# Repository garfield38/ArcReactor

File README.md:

# ArcReactor
Arc Reactor replica made with Attiny85 and WS2812B LEDs

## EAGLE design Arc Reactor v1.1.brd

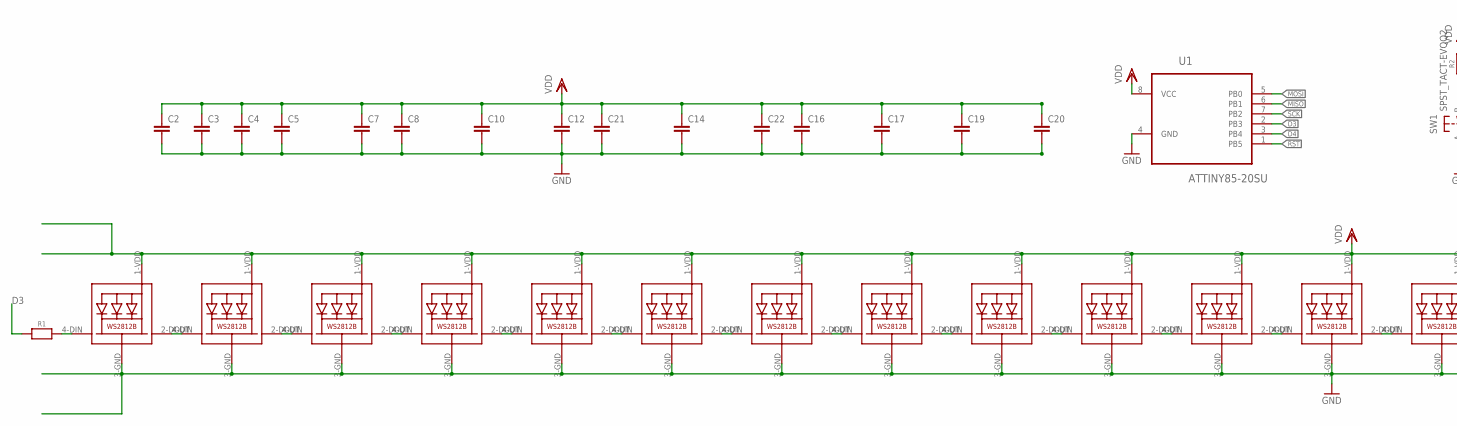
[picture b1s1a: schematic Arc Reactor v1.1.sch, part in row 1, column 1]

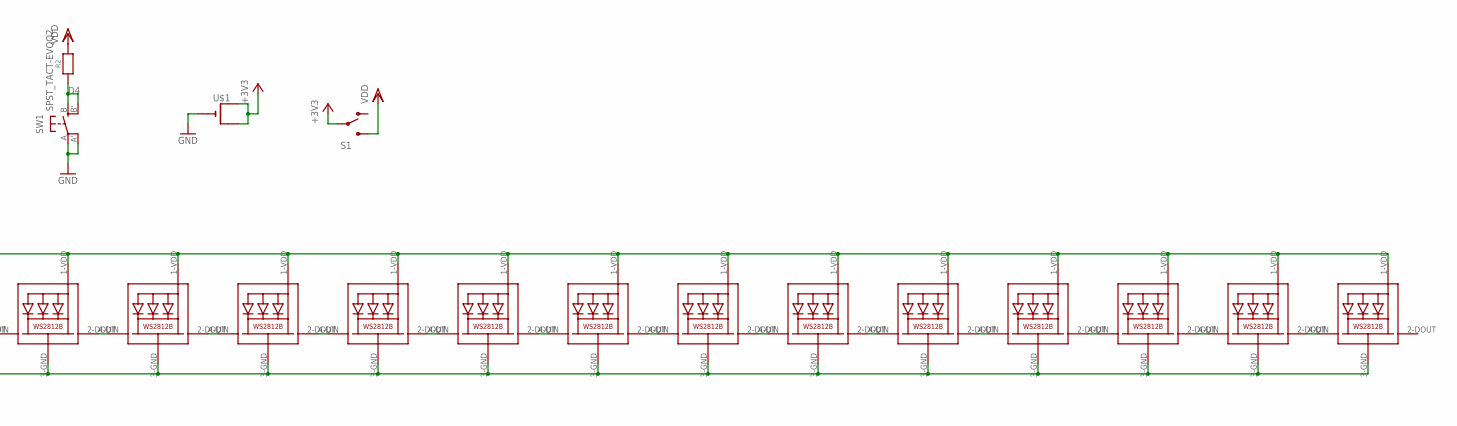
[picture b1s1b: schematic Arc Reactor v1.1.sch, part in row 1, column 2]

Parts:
C2, C3, C4, C5, C7, C8, C10, C12, C14, C16, C17, C19, C20, C21, C22: C-EUC0603; C0603; MOUSER# 77-VJ0603Y104JXQPBC
LED1, LED3, LED4, LED5, LED6, LED7, LED8, LED9, LED10, LED11, LED12, LED13, LED14, LED15, LED16, LED17, LED18, LED19, LED20, LED21, LED22, LED23, LED24, LED25, LED26: WS2812B5050; WS2812B
R1, R2: RESISTOR_0603_NOOUT; 0603-NO
S1: SWITCH-SPDTSMD2; SWITCH-SPDT-SMD; MOUSER# 611-JS102011SAQN
SW1: SPST_TACT-EVQQ2; EVQ-Q2
U1: ATTINY85-20SU; SOIC127P798X216-8N; MOUSER# 556-ATTINY85-20SU
U$1: CR2032SMT; CR2032-SMD

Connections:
+3V3: S1.2, U$1.+$1 (+), U$1.+$2 (+1)
D3: R1.1, U1.2 (PB3)
D4: R2.1, SW1.B (S), SW1.B' (S1), U1.3 (PB4)
GND: C2.2, C3.2, C4.2, C5.2, C7.2, C8.2, C10.2, C12.2, C14.2, C16.2, C17.2, C19.2, C20.2, C21.2, C22.2, LED1.3-GND (GND), LED3.3-GND (GND), LED4.3-GND (GND), LED5.3-GND (GND), LED6.3-GND (GND), LED7.3-GND (GND), LED8.3-GND (GND), LED9.3-GND (GND), LED10.3-GND (GND), LED11.3-GND (GND), LED12.3-GND (GND), LED13.3-GND (GND), LED14.3-GND (GND), LED15.3-GND (GND), LED16.3-GND (GND), LED17.3-GND (GND), LED18.3-GND (GND), LED19.3-GND (GND), LED20.3-GND (GND), LED21.3-GND (GND), LED22.3-GND (GND), LED23.3-GND (GND), LED24.3-GND (GND), LED25.3-GND (GND), LED26.3-GND (GND), SW1.A, SW1.A' (P1), U1.4 (GND), U$1.-
MISO: U1.6 (PB1)
MOSI: U1.5 (PB0)
unnamed: LED1.2-DOUT (DO), LED3.4-DIN (DI)
unnamed: LED3.2-DOUT (DO), LED4.4-DIN (DI)
unnamed: LED4.2-DOUT (DO), LED5.4-DIN (DI)
unnamed: LED5.2-DOUT (DO), LED6.4-DIN (DI)
unnamed: LED6.2-DOUT (DO), LED7.4-DIN (DI)
unnamed: LED7.2-DOUT (DO), LED8.4-DIN (DI)
unnamed: LED8.2-DOUT (DO), LED9.4-DIN (DI)
unnamed: LED9.2-DOUT (DO), LED10.4-DIN (DI)
unnamed: LED10.2-DOUT (DO), LED11.4-DIN (DI)
unnamed: LED11.2-DOUT (DO), LED12.4-DIN (DI)
unnamed: LED12.2-DOUT (DO), LED13.4-DIN (DI)
unnamed: LED13.2-DOUT (DO), LED14.4-DIN (DI)
unnamed: LED14.2-DOUT (DO), LED15.4-DIN (DI)
unnamed: LED15.2-DOUT (DO), LED16.4-DIN (DI)
unnamed: LED16.2-DOUT (DO), LED17.4-DIN (DI)
unnamed: LED17.2-DOUT (DO), LED18.4-DIN (DI)
unnamed: LED18.2-DOUT (DO), LED19.4-DIN (DI)
unnamed: LED19.2-DOUT (DO), LED20.4-DIN (DI)
unnamed: LED20.2-DOUT (DO), LED21.4-DIN (DI)
unnamed: LED21.2-DOUT (DO), LED22.4-DIN (DI)
unnamed: LED22.2-DOUT (DO), LED23.4-DIN (DI)
unnamed: LED23.2-DOUT (DO), LED24.4-DIN (DI)
unnamed: LED24.2-DOUT (DO), LED25.4-DIN (DI)
unnamed: LED25.2-DOUT (DO), LED26.4-DIN (DI)
unnamed: LED1.4-DIN (DI), R1.2
RST: U1.1 (PB5)
SCK: U1.7 (PB2)
VDD: C2.1, C3.1, C4.1, C5.1, C7.1, C8.1, C10.1, C12.1, C14.1, C16.1, C17.1, C19.1, C20.1, C21.1, C22.1, LED1.1-VDD (VDD), LED3.1-VDD (VDD), LED4.1-VDD (VDD), LED5.1-VDD (VDD), LED6.1-VDD (VDD), LED7.1-VDD (VDD), LED8.1-VDD (VDD), LED9.1-VDD (VDD), LED10.1-VDD (VDD), LED11.1-VDD (VDD), LED12.1-VDD (VDD), LED13.1-VDD (VDD), LED14.1-VDD (VDD), LED15.1-VDD (VDD), LED16.1-VDD (VDD), LED17.1-VDD (VDD), LED18.1-VDD (VDD), LED19.1-VDD (VDD), LED20.1-VDD (VDD), LED21.1-VDD (VDD), LED22.1-VDD (VDD), LED23.1-VDD (VDD), LED24.1-VDD (VDD), LED25.1-VDD (VDD), LED26.1-VDD (VDD), R2.2, S1.3 (S), U1.8 (VCC)

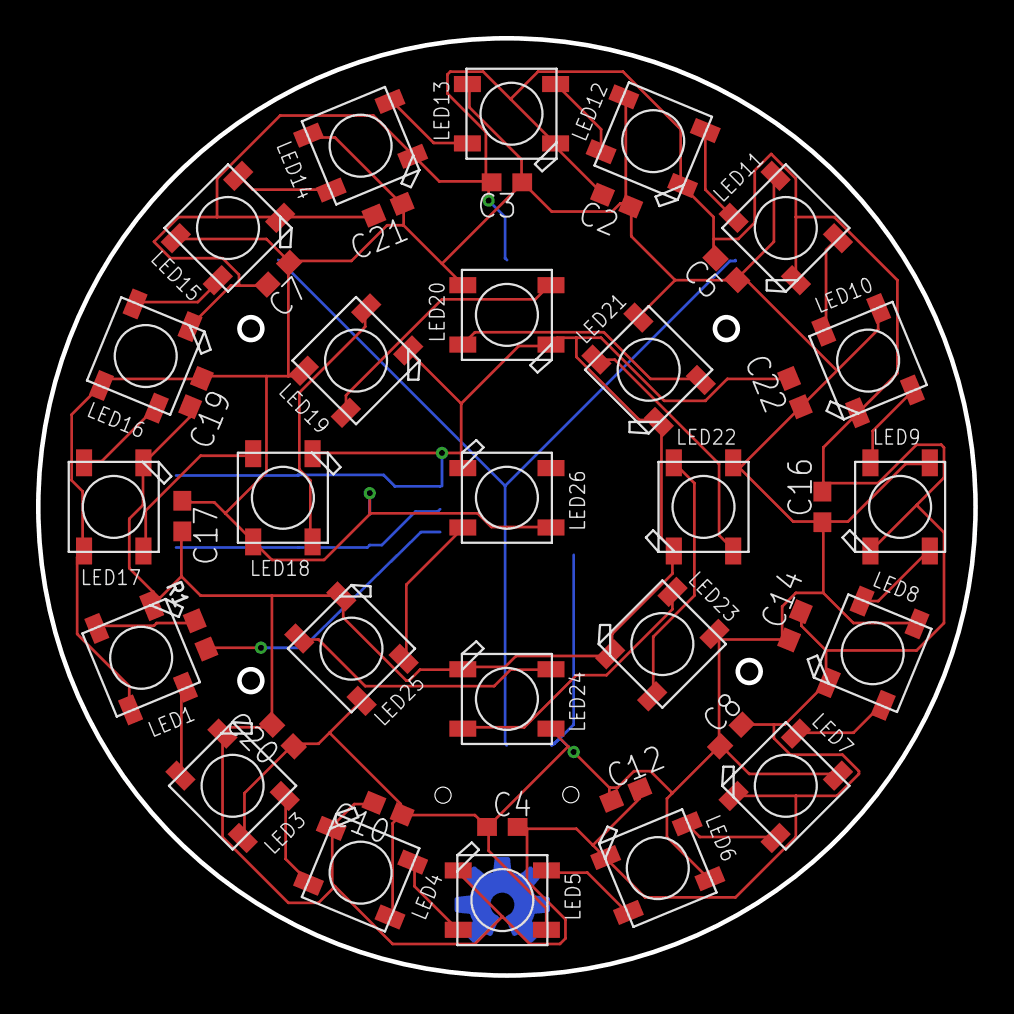
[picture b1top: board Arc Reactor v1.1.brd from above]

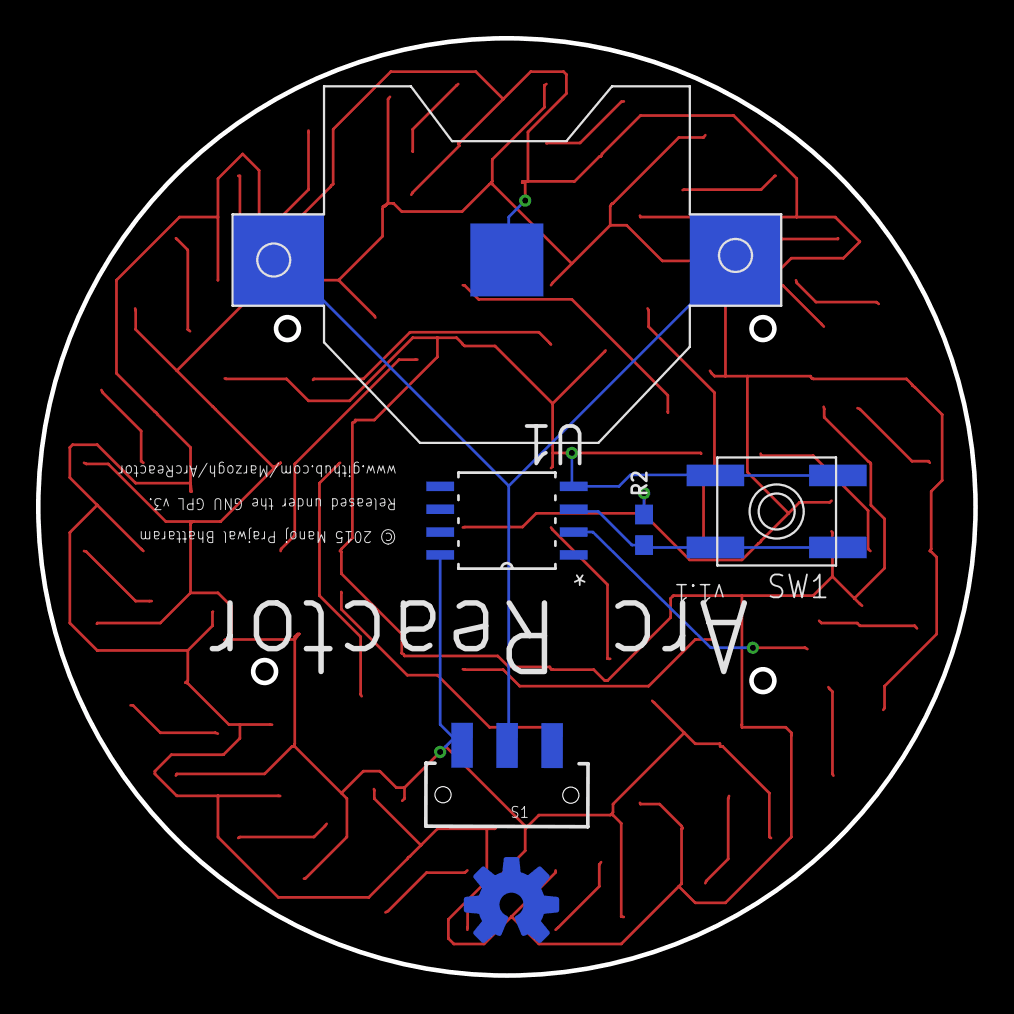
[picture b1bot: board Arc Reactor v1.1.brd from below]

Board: 2 copper layers, 52.1 x 52.1 mm, 47 parts (6 on the bottom side), 30 nets.

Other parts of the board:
U$2: OSHWLOGO_TOP_0.2

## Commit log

2015-05-09 Schematics, Board design and Gerber files added
2015-06-10 add pushbutton
    add push button to select mode

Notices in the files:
Arc Reactor v1.1.brd:
© 2015 Manoj Prajwal Bhattaram
Released under the GNU GPL v3.
parts and their libraries:
SparkFun-Electromechanical: Licensing: Creative Commons ShareAlike 4.0 International - https://creativecommons.org/licenses/by-sa/4.0
microbuilder: This work is placed in the public domain, and may be freely used for commercial and non-commercial work with the following conditions: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
